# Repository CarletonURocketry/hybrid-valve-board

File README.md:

# Hybrid Valve Board

This board keeps the 3 flight valves powered in flight when disconnected from the ground systems in order
to not dump nitrous oxidizer anywhere except the combustion chamber. Otherwise, we don't fly very long.

The board is mainly controlled by an ATTiny85 MCU, and is powered using a Li-Ion battery as well as a 24V (between
20-24V) rail for supplying the solenoids. It is essentially a fancy switch.

You can view the PCB using KiCanvas [here](https://kicanvas.org/?github=https%3A%2F%2Fgithub.com%2FCarletonURocketry%2Fhybrid-valve-board).

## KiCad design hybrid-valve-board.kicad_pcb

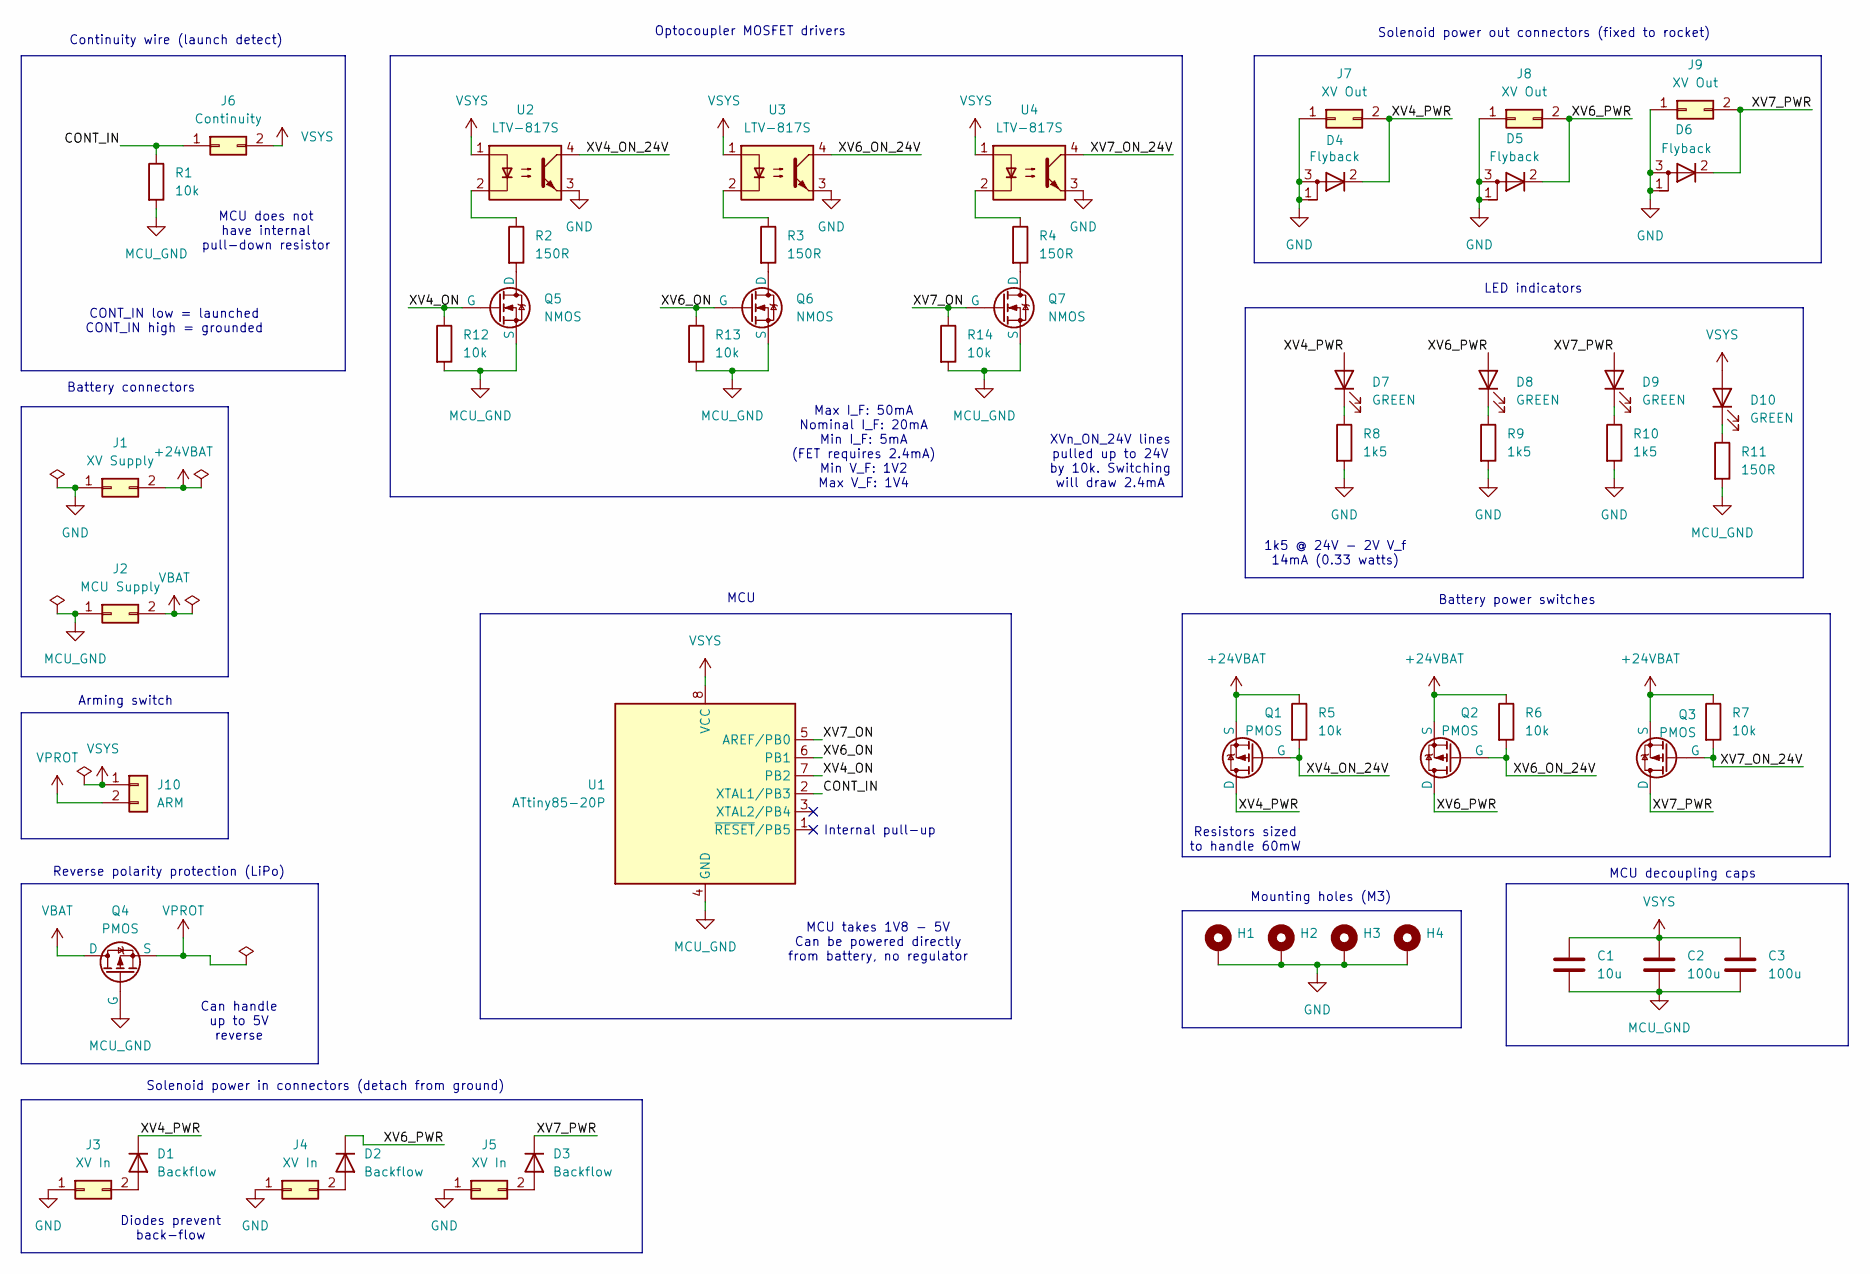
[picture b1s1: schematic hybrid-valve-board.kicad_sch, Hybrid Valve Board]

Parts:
C1: 10u; C_0805_2012Metric; MPN EMK212BB7106KG-T
C2, C3: 100u; C_0805_2012Metric; MPN CL21A107MQYNNWE
D1, D2, D3: Backflow; D_SOD-128; MPN RBR3LAM60BTR
D4, D5, D6: Flyback; TO-263-2; MPN RFN10NS4STL
D7, D8, D9, D10: GREEN; LED_0805_2012Metric_Pad1.15x1.40mm_HandSolder; MPN HSMG-C170
H1, H2, H3, H4: MountingHole_3.2mm_M3_DIN965_Pad
J1: XV Supply; 1726480102; MPN 172648-0102
J2: MCU Supply; JST_PH_S2B-PH-SM4-TB_1x02-1MP_P2.00mm_Horizontal; MPN 172648-0102
J3, J4, J5: XV In; 1726480102; MPN 172648-0102
J6: Continuity; 1726480102; MPN 172648-0102
J7, J8, J9: XV Out; 1726480102; MPN 172648-0102
J10: ARM; 1726480102; MPN 172648-0102
Q1, Q2, Q3: PMOS; TO-252-2; MPN FQD5P20TM
Q4: PMOS; SOT-23-3; MPN SI2329DS-T1-GE3
Q5, Q6, Q7: NMOS; SOT-23-3; MPN BSH105,215
R1, R5, R6, R7, R12, R13, R14: 10k; R_0805_2012Metric_Pad1.20x1.40mm_HandSolder; MPN CRCW080510K0FKEA
R2, R3, R4, R11: 150R; R_0805_2012Metric_Pad1.20x1.40mm_HandSolder; MPN RK73B2ATTDD151J
R8, R9, R10: 1k5; R_0805_2012Metric_Pad1.20x1.40mm_HandSolder; MPN SDR10EZPJ152
U1: ATtiny85-20P; DIP-8_W7.62mm_Socket; MPN ATTINY85-20PU
U2, U3, U4: LTV-817S; SMDIP-4_W9.53mm; MPN LTV-817S

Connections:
+24VBAT: J1.2, Q1.3 (S), Q2.3 (S), Q3.3 (S), R5.1, R6.1, R7.1
/CONT_IN: J6.1, R1.1, U1.2 (XTAL1/PB3)
/XV4_ON: Q5.1 (G), R12.1, U1.7 (PB2)
/XV4_ON_24V: Q1.1 (G), R5.2, U2.4
/XV4_PWR: D1.1 (K), D4.2 (K), D7.2 (A), J7.2, Q1.2 (D)
/XV6_ON: Q6.1 (G), R13.1, U1.6 (PB1)
/XV6_ON_24V: Q2.1 (G), R6.2, U3.4
/XV6_PWR: D2.1 (K), D5.2 (K), D8.2 (A), J8.2, Q2.2 (D)
/XV7_ON: Q7.1 (G), R14.1, U1.5 (AREF/PB0)
/XV7_ON_24V: Q3.1 (G), R7.2, U4.4
/XV7_PWR: D3.1 (K), D6.2 (K), D9.2 (A), J9.2, Q3.2 (D)
GND: D4.1 (A), D4.3 (A), D5.1 (A), D5.3 (A), D6.1 (A), D6.3 (A), H1.1, H2.1, H3.1, H4.1, J1.1, J3.1, J4.1, J5.1, J7.1, J8.1, J9.1, R8.2, R9.2, R10.2, U2.3, U3.3, U4.3
MCU_GND: C1.2, C2.2, C3.2, J2.1, Q4.1 (G), Q5.2 (S), Q6.2 (S), Q7.2 (S), R1.2, R11.2, R12.2, R13.2, R14.2, U1.4 (GND)
unnamed: D1.2 (A), J3.2
unnamed: D2.2 (A), J4.2
unnamed: D3.2 (A), J5.2
unnamed: D7.1 (K), R8.1
unnamed: D8.1 (K), R9.1
unnamed: D9.1 (K), R10.1
unnamed: D10.1 (K), R11.1
unnamed: Q5.3 (D), R2.2
unnamed: Q6.3 (D), R3.2
unnamed: Q7.3 (D), R4.2
unnamed: R2.1, U2.2
unnamed: R3.1, U3.2
unnamed: R4.1, U4.2
VBAT: J2.2, Q4.3 (D)
VPROT: J10.2, Q4.2 (S)
VSYS: C1.1, C2.1, C3.1, D10.2 (A), J6.2, J10.1, U1.8 (VCC), U2.1, U3.1, U4.1

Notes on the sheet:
Mounting holes (M3)
XVn_ON_24V lines pulled up to 24V by 10k. Switching will draw 2.4mA
MCU decoupling caps
Arming switch
Resistors sized to handle 60mW
Diodes prevent back-flow
Reverse polarity protection (LiPo)
Continuity wire (launch detect)
Battery connectors
Optocoupler MOSFET drivers
MCU
Solenoid power in connectors (detach from ground)
MCU takes 1V8 - 5V Can be powered directly from battery, no regulator
Can handle up to 5V reverse
Max I_F: 50mA Nominal I_F: 20mA Min I_F: 5mA (FET requires 2.4mA) Min V_F: 1V2 Max V_F: 1V4
Solenoid power out connectors (fixed to rocket)
MCU does not have internal pull-down resistor
LED indicators
Battery power switches
1k5 @ 24V - 2V V_f 14mA (0.33 watts)
CONT_IN low = launched CONT_IN high = grounded
Internal pull-up

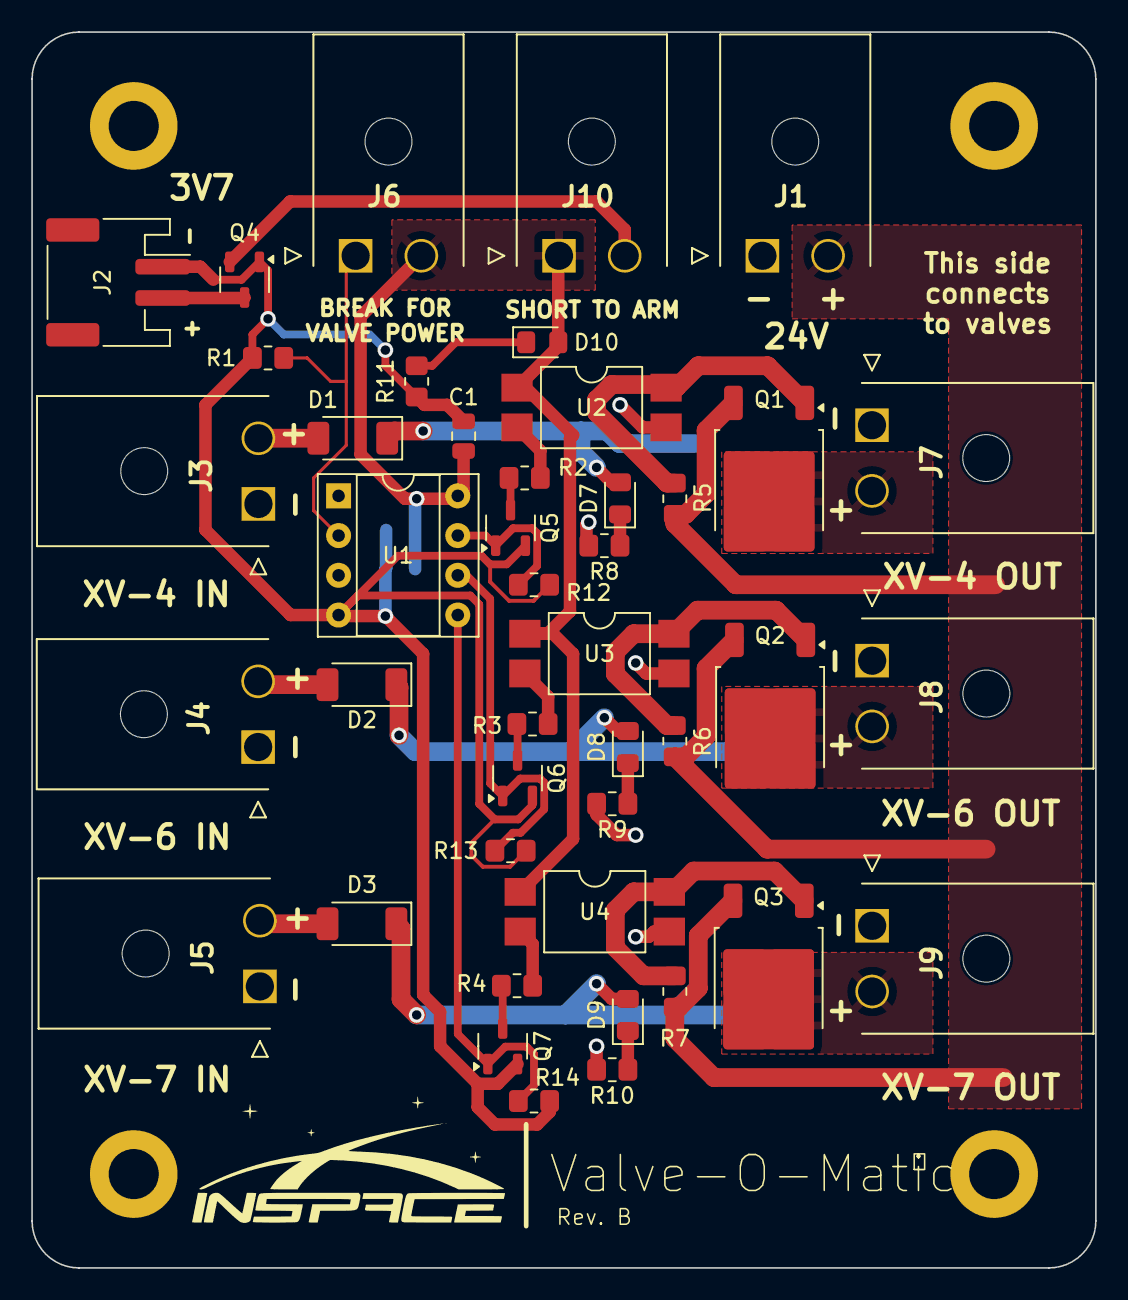
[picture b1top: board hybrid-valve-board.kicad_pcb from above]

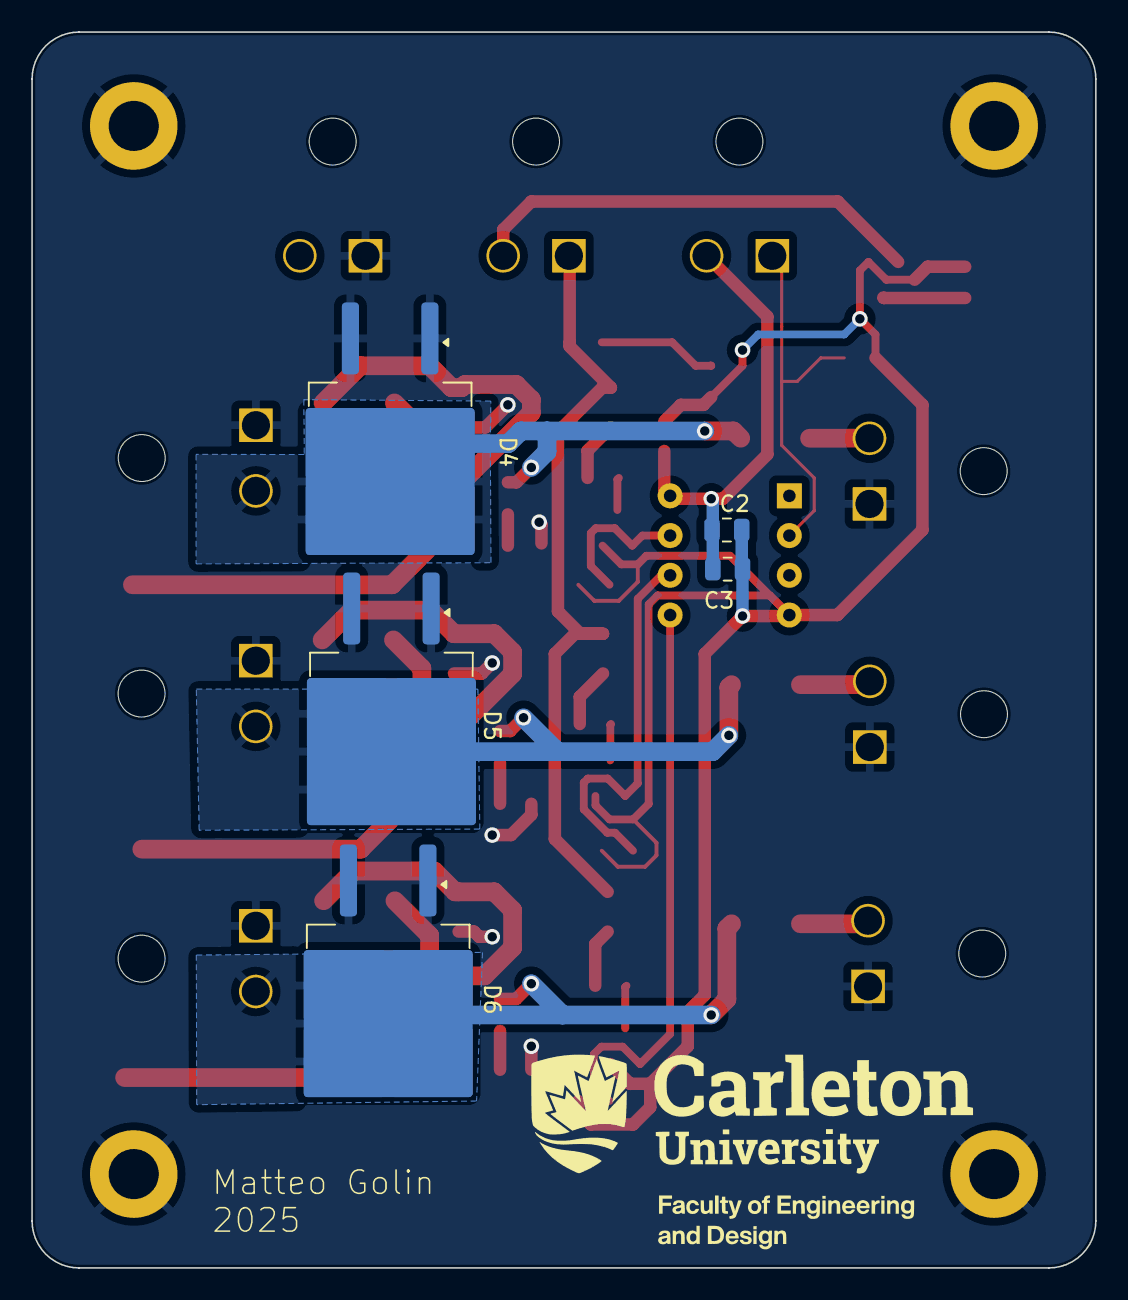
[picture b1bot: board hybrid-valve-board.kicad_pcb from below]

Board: 2 copper layers, 68.0 x 79.0 mm, 52 parts (5 on the bottom side), 29 nets.

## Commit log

2025-06-26 Initial commit.
2025-06-26 Warranty text
2025-06-26 KiCanvas link
2025-06-26 Picture of board
2025-06-26 Saved schematic change
2025-06-28 Added: reverse polarity protection for MCU, arming LED and PMOS switching
2025-06-28 Update BOM
2025-06-28 Slightly better copper pours
2025-06-28 Better pour
2025-06-28 Move arming LED closer to arming switch
2025-06-28 Updated image
2025-07-01 Update backflow diodes to identical package that can handle 1.5A at 75C
2025-07-01 Added power decoupling capacitors for MCU
2025-07-01 Thickened valve power traces from ground systems
2025-07-11 Revision B, with correct connections for the PMOS switches :/
2025-07-11 Move LED indicators to power line to avoid interfering with gate signal
2025-07-12 Use NMOS to flip opto-coupler
2025-07-12 Add pull-down resistor on NMOS gate
